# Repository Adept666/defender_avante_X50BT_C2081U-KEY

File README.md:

# defender_avante_X50BT_C2081U-KEY

Проект состоит из принципиальной схемы и чертежа печатного узла (ПУ) индикации и управления C2081U-KEY акустической системы Defender Avante X50BT. Чертежи созданы с помощью программы [KiCad](http://kicad-pcb.org) и предназначены для самостоятельного изготовления данного ПУ в случае выхода оригинального ПУ из строя и отсутствия возможности его ремонта.

## Requirements (Требования)

Работа с проектом осуществляется в программе [KiCad](http://kicad-pcb.org).

Для просмотра принципиальной схемы необходимо подключить следующие библиотеки символов:
* [KCL](http://github.com/Adept666/KCL) (файлы KCL.lib и ICL_TITAN_MICRO_ELECTRONICS.lib из репозитория [KCL](http://github.com/Adept666/KCL));
* библиотеку данного проекта (файл defender_avante_X50BT_C2081U-KEY.lib из данного репозитория).

Для просмотра чертежа ПУ подключение библиотек не требуется, так как все использованные футпринты вшиты в файл defender_avante_X50BT_C2081U-KEY.kicad_pcb. При необходимости футпринты могут быть найдены в библиотеке [KCL](http://github.com/Adept666/KCL).

## Author (Автор)

Igor Ivanov

## License (Лицензия)

This project is licensed under GNU General Public License v3.0 or later

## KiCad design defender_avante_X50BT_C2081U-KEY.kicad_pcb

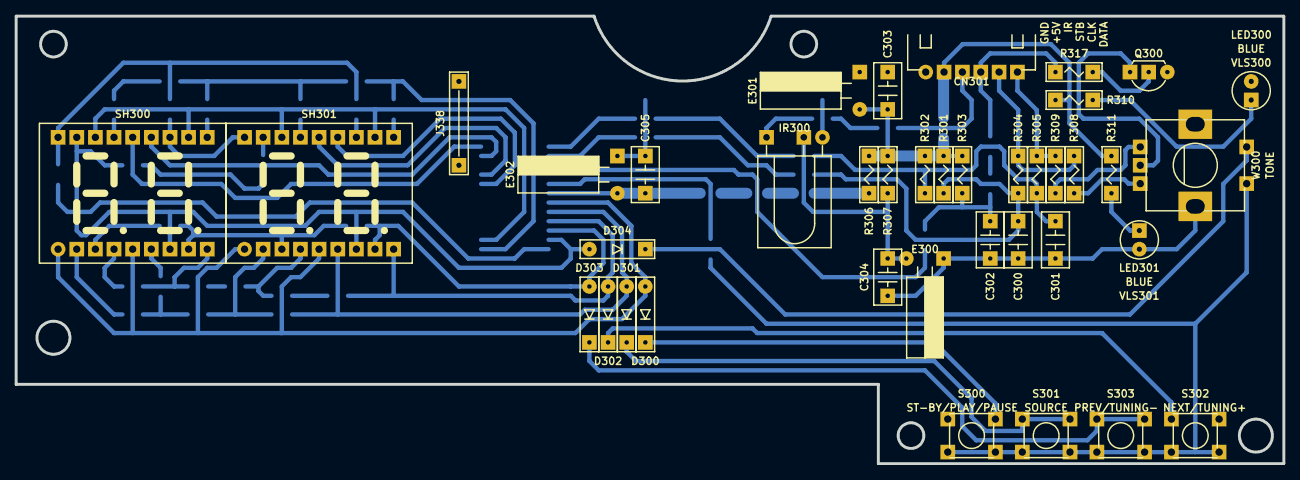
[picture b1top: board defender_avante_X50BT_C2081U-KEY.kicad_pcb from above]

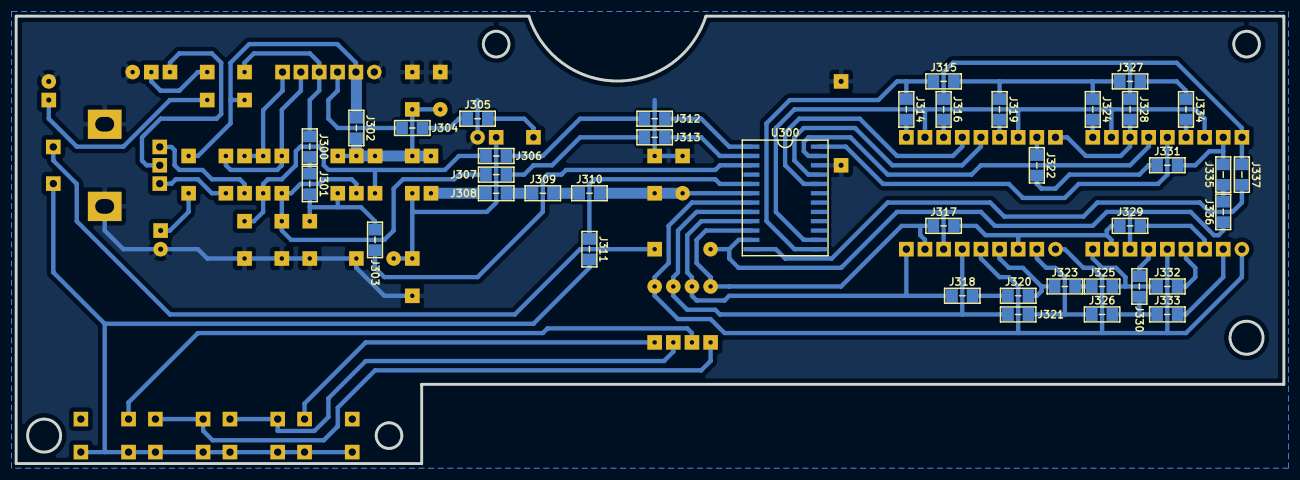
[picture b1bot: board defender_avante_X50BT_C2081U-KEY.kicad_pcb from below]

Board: 2 copper layers, 172.7 x 61.0 mm, 80 parts (39 on the bottom side), 34 nets.

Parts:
C300, C301, C302, C303, C304, C305: CAPACITOR_NON-POLARIZED; C-DISK-D04.2-T03.0-P05.08-d0.5
CN301: CONNECTOR_M_006_20_SPECIAL; CON-CWF-6RA
D300, D301, D302, D303, D304: DIODE_GENERAL; P-DO-35
E300: CAPACITOR_POLARIZED; CP-RADIAL-D05.0-P02.0-d0.5-L11-HD
E301, E302: CAPACITOR_POLARIZED; CP-RADIAL-D05.0-P02.0-d0.5-L11-HU
IR300: IC_IRR; IRR-CAST-GND-VCC-OUT-H
J300, J301, J302, J303, J304, J305, J306, J307, J308, J309, J310, J311, J312, J313, J314, J315, J316, J317, J318, J319, J320, J321, J322, J323, J324, J325, J326, J327, J328, J329, J330, J331, J332, J333, J334, J335, J336, J337: JUMPER; J-SM-1206
J338: JUMPER; J-TH-d0.6-P11.43
LED300, LED301: DIODE_LIGHT-EMITTING_LEFT; LED-ROUND-03.0-UNI-SH-SPACER
Q300: BJT_NPN_GENERAL; P-TO-92-E-B-C
R301, R302, R303, R304, R305, R306, R307, R308, R309, R310, R311, R317: RESISTOR_GENERAL; R-MFR-12
S300, S301, S302, S303: SWITCH_BUTTON_NON-LOCK_01P_01T_NO; SW-06XXX
SH300, SH301: DIODE_7SEG_2DIG_CC_S; LED-7SEG-DC56-11
U300: TM1668; P-SO-24W
VLS300, VLS301: VIRTUAL_LED-SPACER; VLS-BR
W300: ENCODER_CONTACTING_INC_B_C; ENC-PEC12R-4-F-S

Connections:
/A: SH300.1AA, SH300.2AA, SH301.1AA, SH301.2AA, U300.14
/B: J314.J, J315.J, J319.J, J324.J, J327.J, J334.J, SH300.1AB, SH300.2AB, SH301.1AB, SH301.2AB, U300.13
/C: D303.A, J317.J, J329.J, SH300.1AC, SH300.2AC, SH301.1AC, SH301.2AC, U300.10
/CLK: CN301.5, R304.1, R308.2
/D: D301.A, J321.J, J326.J, J330.J, J333.J, SH300.1AD, SH300.2AD, SH301.1AD, SH301.2AD, U300.8
/DATA: CN301.6, R305.1, R309.2
/DIG1: SH300.1C, U300.24
/DIG2: SH300.2C, U300.23
/DIG3: SH301.1C, U300.21
/DIG4: SH301.2C, U300.20
/DP: D302.A, J318.J, J320.J, J323.J, J325.J, J332.J, SH300.1AH, SH300.2AH, SH301.1AH, SH301.2AH, U300.9
/E: D300.A, SH300.1AE, SH300.2AE, SH301.1AE, SH301.2AE, U300.7
/F: J316.J, J328.J, J337.J, SH300.1AF, SH300.2AF, SH301.1AF, SH301.2AF, U300.12
/G: D304.A, J322.J, J331.J, J335.J, J336.J, SH300.1AG, SH300.2AG, SH301.1AG, SH301.2AG, U300.11
/IC_+5V: C305.1, E302.+, J308.J, J309.J, J310.J, R306.1, U300.6
/IC_CLK: C300.1, J307.J, J313.J, R301.1, R304.2, U300.2
/IC_DATA: C301.1, J306.J, J312.J, R302.1, R305.2, U300.1
/IR: CN301.3, IR300.OUT, J304.J, J305.J
/K2: J311.J, S300.NO, S301.NO, S302.NO, S303.NO, U300.5, W300.NO
/STB: C302.1, CN301.4, J300.J, J301.J, J303.J, R303.1, R317.1, U300.3
COM: C300.2, C301.2, C302.2, C303.2, C304.2, C305.2, CN301.1, E300.-, E301.-, E302.-, IR300.GND, J338.J, LED300.C, LED301.C, Q300.E, U300.22, W300.0
unnamed: C304.1, E300.+, IR300.VCC, R307.1
unnamed: D300.C, S300.COM
unnamed: D301.C, S301.COM
unnamed: D302.C, S302.COM
unnamed: D303.C, S303.COM
unnamed: D304.C, W300.COM
unnamed: LED300.A, R310.1
unnamed: LED301.A, R311.1
unnamed: Q300.B, R317.2
unnamed: Q300.C, W300.C
unnamed: R308.1, W300.B
unnamed: R309.1, W300.A
V: C303.1, CN301.2, E301.+, J302.J, R301.2, R302.2, R303.2, R306.2, R307.2, R310.2, R311.2

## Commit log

2018-12-17 Добавлен файл лицензии
2018-12-17 Впервые загружены файлы проекта
2019-02-17 Буквенная нумерация составных частей компонентов заменена на цифровую
2019-02-17 Свойства текстовых полей УГО приведены к единообразию. Показана мощность резисторов
2019-02-17 Удалены соединительные точки на шине
2019-02-17 Отредактирована библиотека проекта
2019-02-17 Применены собственные символы общей точки и питания
2019-02-17 Создано изображение схемы
2019-02-17 Создан файл README.md
2019-02-18 В связи с доработкой библиотеки обновлены футпринты диодов и светодиодов
2019-02-18 Корректно выбраны значения свойсва Placement Type футпринтов
2019-02-18 Обновлены футпринты (удалены примитивы на слое F.Paste)
2019-02-18 Повторно выбраны значения свойсва Placement Type футпринтов
2019-04-11 Скорректированы размеры платы, положение монтажных отверстий, кнопок, энкодера и светодиодов. Заменены держатели светодиодов
2019-04-23 В схему добавлены токоограничивающие резисторы R318...R325
2019-04-23 Положение элементов и печатных дорожек скорректировано с учётом новых размеров платы
2019-04-24 Обновлено УГО ИМС
2019-05-15 Основные надписи схемы и платы дополнены комментариями о лицензии
2019-05-15 Исправлены связи новых резисторов. Удалены примитивы на слоях F.Cu и F.Mask
2019-05-16 Токоограничивающие резисторы размещены на плате. Плата отредактирована
2019-05-23 Обновлено УГО ИМС. ИМС и обвязка временно размещены за пределами листа
2019-05-23 Удалён поролоновый держатель
2019-05-23 Занулены координаты футпринта E300
2019-05-23 В схему включены виртуальные держатели для светодиодов
2019-05-23 Применён символ энкодера с выводом корпуса
2019-06-03 Удалена лишняя перемычка J314
2019-06-04 Схема и плата оформлены корректно
2019-09-02 Обновлена библиотека проекта
2019-09-02 Повёрнуты светодиоды. Залочены футпринты энкодера и разъёма
2019-09-04 Проект скорректирован с учётом изменений в УГО и ФП переключателей
2019-09-04 Плата скорректирована с учётом изменений в ФП семисегментных индикаторов
2019-09-06 Перемещено одно из монтажных отверстий
2019-09-06 Удалена поясняющая надпись
2019-09-06 Осуществлён переход к ревизии 3
2019-09-16 Обновлены футпринты R-MFR-12
2019-09-24 Ширина шины питания увеличена с 0.6 до 1.5 мм
2019-11-11 Удалены резисторы R318…R325
2020-03-05 Добавлена выводная перемычка J338
2020-03-05 Создан файл sym-lib-table
2020-03-05 Положение дорожек скорректировано в связи с удалением резисторов. Удалены верхние слои КП J338
2020-03-05 Создан земляной полигон
2020-03-05 Удалено отчество в README.md
2020-03-05 Удалено отчество на чертежах
2020-03-05 Удалены резервные копии
2020-06-28 Схема и плата обновлены в связи с переименованием ФП перемычек
2020-06-28 Создано изображение печатного узла
2020-06-28 Расширено описание проекта
